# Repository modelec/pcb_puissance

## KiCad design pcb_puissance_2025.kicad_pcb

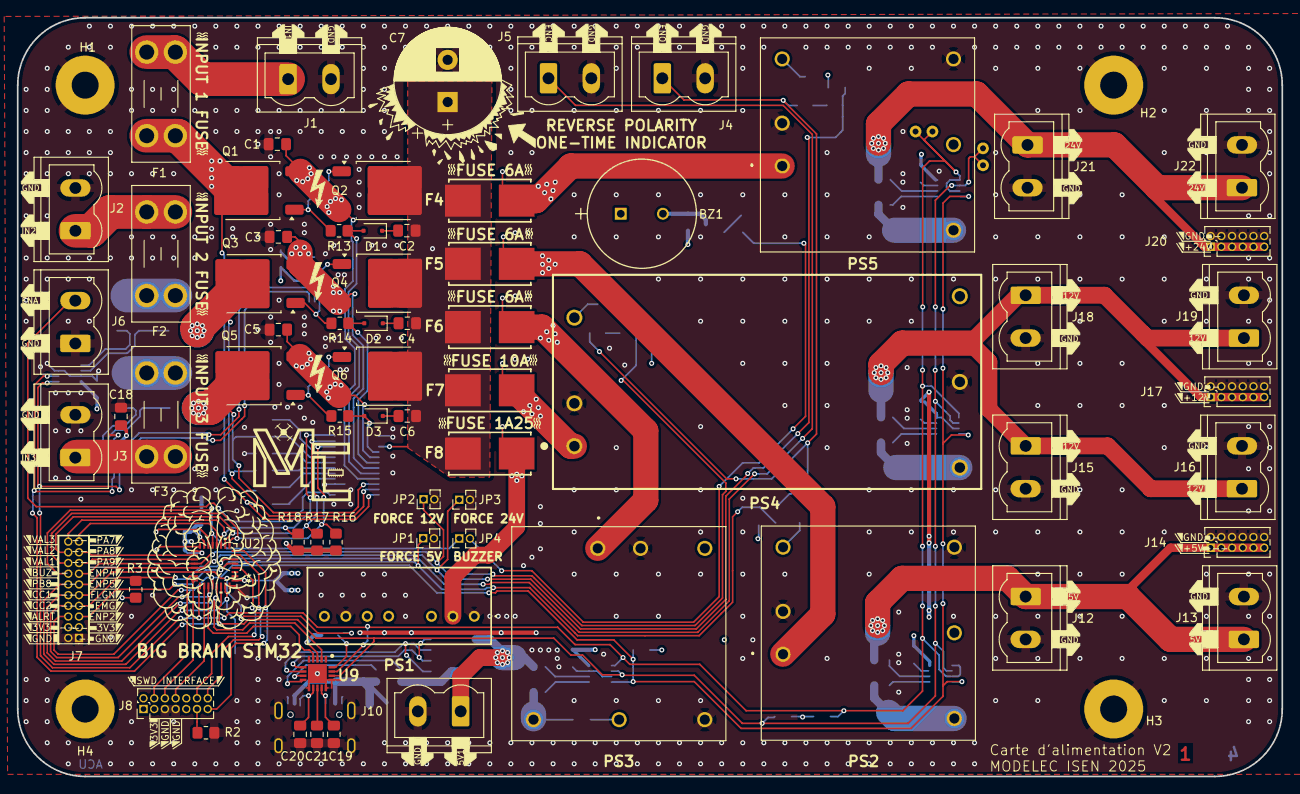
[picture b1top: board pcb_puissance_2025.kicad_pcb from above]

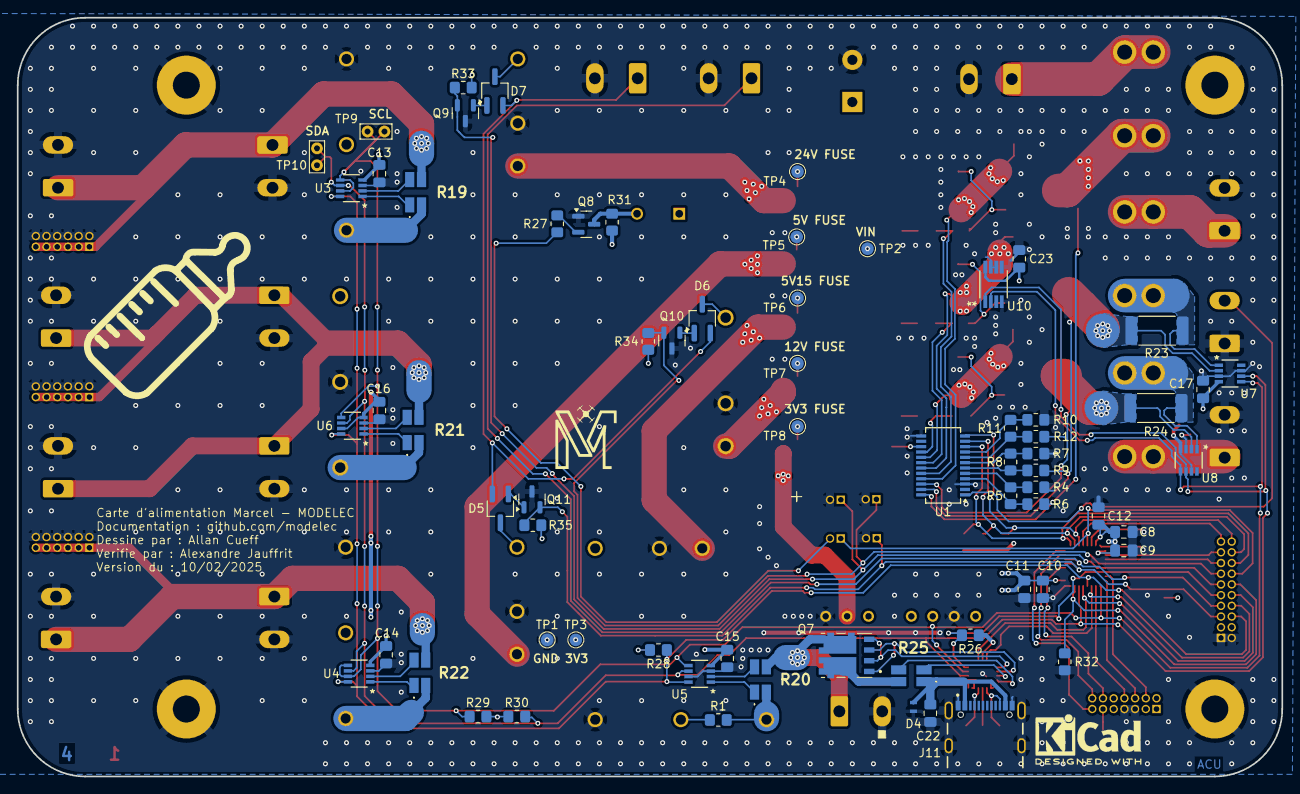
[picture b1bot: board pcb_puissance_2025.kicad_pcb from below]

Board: 4 copper layers, 150.0 x 90.0 mm, 139 parts (67 on the bottom side), 96 nets.

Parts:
BZ1: Buzzer; XTAL_PS1240P02BT_TDK
C1, C3, C5: 0u39; C_0805_2012Metric_Pad1.18x1.45mm_HandSolder
C2, C4, C6: 39n; C_0805_2012Metric_Pad1.18x1.45mm_HandSolder
C7: 1000u; CP_Radial_D12.5mm_P5.00mm
C8: 10n; C_0805_2012Metric_Pad1.18x1.45mm_HandSolder
C9, C10, C13, C14, C15, C16, C17, C18, C21, C23: 100n; C_0805_2012Metric_Pad1.18x1.45mm_HandSolder
C11: 4u7; C_0805_2012Metric_Pad1.18x1.45mm_HandSolder
C12: 1u; C_0805_2012Metric_Pad1.18x1.45mm_HandSolder
C19, C20: 330p; C_0805_2012Metric_Pad1.18x1.45mm_HandSolder
C22: 2u2; C_0805_2012Metric_Pad1.18x1.45mm_HandSolder
D1, D2, D3: BAT54J; D_SOD-323F
D4: ESDA25P35-1U1M; QFN1610_STM
D5, D6, D7: D_Dual_CommonAnode_AKK_Parallel; TSOT-23_HandSoldering
F1: 10A; Fuseholder_Blade_Mini_Keystone_3568
F2, F3: 20A; Fuseholder_Blade_Mini_Keystone_3568
F4, F5, F6: 6A; 01550900M
F7: 10A; 01550900M
F8: 1A25; 01550900M
H1, H2, H3, H4: MountingHole_Pad; MountingHole_3.2mm_M3_Pad
J1, J2, J3, J4, J5, J6, J10, J12, J13, J15, J16, J18, J19, J21, J22: 1755736; PhoenixContact_MSTBVA_2,5_2-G-5,08_1x02_P5.08mm_Vertical
J7: Conn_02x10_Odd_Even; PinHeader_2x10_P1.27mm_Vertical
J8: Conn_ST_STDC14; PinHeader_2x07_P1.27mm_Vertical
J11: USB_C_Receptacle_USB2.0_16P; GCT_USB4105-GF-A
J14, J17, J20: Conn_02x06_Odd_Even; PinHeader_2x06_P1.27mm_Vertical
JP1, JP2, JP3: Jumper_2_Open; PinHeader_1x02_P1.27mm_Vertical
JP4: Jumper_2_Bridged; PinHeader_1x02_P1.27mm_Vertical
PS1: TMR_6-2410WI; TMR60510
PS2, PS3: THN_30-2411WI; THN301211
PS4: TEN_50-2412WI; TEN_50-2411
PS5: THN_30-2415WI; THN301211
Q1, Q2, Q3, Q4, Q5, Q6: SUD50P06-15; TO-252-2
Q7: STL40DN3LLH5; TRANS_STL40DN3LLH5
Q8: NPN; SOT-23
Q9, Q10, Q11: NMOS; SOT-23
R1: 82k; R_0805_2012Metric_Pad1.20x1.40mm_HandSolder
R2: 100; R_0805_2012Metric_Pad1.20x1.40mm_HandSolder
R3, R16, R17, R18, R28, R32: 10k; R_0805_2012Metric_Pad1.20x1.40mm_HandSolder
R4: 63k4; R_0805_2012Metric_Pad1.20x1.40mm_HandSolder
R5: 158k; R_0805_2012Metric_Pad1.20x1.40mm_HandSolder
R6: 1960k; R_0805_2012Metric_Pad1.20x1.40mm_HandSolder
R7, R10: 37k4; R_0805_2012Metric_Pad1.20x1.40mm_HandSolder
R8, R11: 78k7; R_0805_2012Metric_Pad1.20x1.40mm_HandSolder
R9, R12: 1180k; R_0805_2012Metric_Pad1.20x1.40mm_HandSolder
R13, R14, R15: 11k5; R_0805_2012Metric_Pad1.20x1.40mm_HandSolder
R19: 62m 0.5%; L4CL1206LR013DNR
R20, R22: 13m 0.5%; L4CL1206LR013DNR
R21: 20m 0.5%; L4CL1206LR013DNR
R23, R24: 4m 0.5%; R_2512_6332Metric_Pad1.40x3.35mm_HandSolder
R25: 7m 1%; L4CL1206LR013DNR
R26: 47k; R_0805_2012Metric_Pad1.20x1.40mm_HandSolder
R27, R31, R33, R34, R35: 1k; R_0805_2012Metric_Pad1.20x1.40mm_HandSolder
R29, R30: 2k2; R_0805_2012Metric_Pad1.20x1.40mm_HandSolder
TP1, TP2, TP3, TP4, TP5, TP6, TP7, TP8: TestPoint; TestPoint_Pad_D1.5mm
TP9, TP10: TestPoint; TestPoint_Bridge_Pitch2.0mm_Drill0.7mm
U1: LTC4417IGN; SSOP-24_3.9x8.7mm_P0.635mm
U2: STM32G491KEU6
U3, U7, U8: INA236BIDDFR; SOT23-8_DDF_TEX
U4, U5, U6: INA236AIDDFR; SOT23-8_DDF_TEX
U9: TCPP02-M18; QFN50P350X350X60-19N-D
U10: MCP9808T-E/MS; MSOP8_MC_MCH

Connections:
/3V3: BZ1.1 (+), C8.1, C9.1, C10.1, C11.1, C12.1, C13.2, C14.2, C15.2, C16.2, C17.1, C18.1, C23.2, J7.3, J7.4, PS1.6 (+VOUT), R3.2, R16.1, R17.1, R18.1, R26.1, R28.2, R29.2, R30.1, R31.1, R33.2, R34.2, R35.2, TP3.1, U2.1 (VDD), U2.15 (VDDA), U2.17 (VDD), U3.4 (VS), U4.4 (VS), U5.4 (VS), U6.4 (VS), U6.7 (A0), U7.4 (VS), U8.4 (VS), U8.7 (A0), U9.3 (VCC_VCONN), U10.8 (VDD)
/Converters/5V: PS2.3 (+VOUT), R22.2
/Converters/5V15: PS3.3 (+VOUT), R1.2, R20.2
/Converters/5V_PILOT: J7.5, JP1.1 (A), Q11.2 (G), R35.1, U2.5 (PA0)
/Converters/12V: PS4.4 (+VOUT), R21.2
/Converters/12V_PILOT: J7.13, JP2.1 (A), Q10.2 (G), R34.1, U2.20 (PA10)
/Converters/24V: PS5.3 (+VOUT), R19.2
/Converters/24V_PILOT: J7.11, JP3.1 (A), Q9.2 (G), R33.1, U2.21 (PA11)
/Converters/EMERGENCY_STOP: D5.2 (K), D6.2 (K), D7.2 (K), J4.1
/Converters/VIN: C2.1, C4.1, C6.1, C7.1, F4.1, F5.1, F6.1, F7.1, F8.1, Q2.2 (D), Q4.2 (D), Q6.2 (D), TP2.1, U1.15 (VOUT)
/Microcontroller/24VALERT: J7.6, R28.1, U2.28 (PB5), U3.8 (ALERT), U4.8 (ALERT), U5.8 (ALERT), U6.8 (ALERT)
/Microcontroller/CC1: J7.10, U2.29 (PB6), U9.2 (CC1)
/Microcontroller/CC2: J7.8, U2.27 (PB4), U9.4 (CC2)
/Microcontroller/FLGN: J7.9, R26.2, U2.22 (PA12), U9.18 (FLGN)
/Microcontroller/PA1: J5.1, J7.7, R3.1, U2.6 (PA1)
/Microcontroller/PA7: J7.19, U2.12 (PA7)
/Microcontroller/PA8: J7.17, U2.18 (PA8)
/Microcontroller/PA9: J7.15, U2.19 (PA9)
/Microcontroller/PB0: J7.14, JP4.1 (A), U2.13 (PB0)
/Microcontroller/PB8: J7.12, R32.2, U2.31 (PB8-BOOT0)
/Microcontroller/SCL: R29.1, TP9.1, U2.25 (PA15), U3.5 (SCL), U3.7 (A0), U4.5 (SCL), U4.7 (A0), U5.5 (SCL), U6.5 (SCL), U7.5 (SCL), U8.5 (SCL), U9.17 (SCL), U10.2 (SCL)
/Microcontroller/SDA: R30.2, TP10.1, U2.30 (PB7), U3.6 (SDA), U4.6 (SDA), U5.6 (SDA), U6.6 (SDA), U7.6 (SDA), U8.6 (SDA), U9.16 (SDA), U10.1 (SDA)
/Microcontroller/VALID1: J7.16, R16.2, U1.10 (~VALID1), U2.9 (PA4)
/Microcontroller/VALID2: J7.18, R17.2, U1.11 (~VALID2), U2.10 (PA5)
/Microcontroller/VALID3: J7.20, R18.2, U1.12 (~VALID3), U2.11 (PA6)
/power_input_selector/EN: J6.2, U1.1 (EN)
/power_input_selector/VIN1: F1.2, Q1.2 (D), R6.1, U1.24 (V1)
/power_input_selector/VIN2: F2.2, R23.2, U7.1 (IN+)
/power_input_selector/VIN3: F3.1, R24.2, U8.1 (IN+)
GND: C1.2, C3.2, C5.2, C7.2, C8.2, C9.2, C10.2, C11.2, C12.2, C13.1, C14.1, C15.1, C16.1, C17.2, C18.2, C19.2, C20.1, C21.1, C22.2, C23.1, D4.2 (A), H1.1, H2.1, H3.1, H4.1, J1.2, J2.2, J3.2, J4.2, J5.2, J6.1, J7.1, J7.2, J8.5 (GND), J8.7 (GND), J10.2, J11.A1_B12 (GND), J11.B1_A12 (GND), J11.SH1 (SHIELD), J11.SH2, J11.SH3, J11.SH4, J12.2, J13.2, J14.2, J14.4, J14.6, J14.8, J14.10, J14.12, J15.2, J16.2, J17.2, J17.4, J17.6, J17.8, J17.10, J17.12, J18.2, J19.2, J20.2, J20.4, J20.6, J20.8, J20.10, J20.12, J21.2, J22.2, JP1.2 (B), JP2.2 (B), JP3.2 (B), PS1.1 (-VIN_(GND)), PS1.7 (-VOUT), PS2.2 (-VIN_(GND)), PS2.5 (-VOUT), PS3.2 (-VIN_(GND)), PS3.5 (-VOUT), PS4.2 (-VIN_(GND)), PS4.5 (-VOUT), PS5.2 (-VIN_(GND)), PS5.5 (-VOUT), Q8.1 (E), Q9.3 (D), Q10.3 (D), Q11.3 (D), R2.2, R4.2, R7.2, R10.2, R32.1, TP1.1, U1.3 (HYS), U1.13 (GND), U2.14 (VSSA), U2.16 (VSS), U2.32 (VSS), U3.3 (GND), U4.3 (GND), U5.3 (GND), U5.7 (A0), U6.3 (GND), U7.3 (GND), U7.7 (A0), U8.3 (GND), U9.10 (GND_1), U9.14 (GND_2), U9.15 (I2C_ADD), U9.19 (GND_3), U10.4 (GND), U10.5 (A2), U10.6 (A1), U10.7 (A0)
unnamed: BZ1.2 (-), Q8.3 (C), R31.2
unnamed: D1.2 (A), R13.2, U1.20 (G1)
unnamed: C2.2, D1.1 (K)
unnamed: D2.2 (A), R14.2, U1.18 (G2)
unnamed: C4.2, D2.1 (K)
unnamed: D3.2 (A), R15.2, U1.16 (G3)
unnamed: C6.2, D3.1 (K)
unnamed: C22.1, D4.1 (K), J11.A4_B9 (VBUS), J11.B4_A9 (VBUS), R25.1
unnamed: D5.3 (A), PS2.6 (REMOTE_ON/OFF)
unnamed: D6.3 (A), PS4.3 (REMOTE_ON/OFF)
unnamed: D7.3 (A), PS5.6 (REMOTE_ON/OFF)
unnamed: F1.1, J1.1
unnamed: F2.1, J2.1
unnamed: F3.2, J3.1
unnamed: J8.11 (GNDDetect), R2.1
unnamed: J8.6 (JCLK/SWCLK), U2.24 (PA14)
unnamed: J8.8 (JTDO/SWO), U2.26 (PB3)
unnamed: J8.4 (JTMS/SWDIO), U2.23 (PA13)
unnamed: J8.13 (VCP_RX), U2.8 (PA3)
unnamed: J8.14 (VCP_TX), U2.7 (PA2)
unnamed: J8.12 (~RST), U2.4 (PG10-NRST)
unnamed: J10.1, Q7.5-6, R20.3
unnamed: C19.1, J11.A5 (CC1), U9.13 (CC1C)
unnamed: C20.2, J11.B5 (CC2), U9.11 (CC2C)
unnamed: J12.1, J13.1, J14.1, J14.3, J14.5, J14.7, J14.9, J14.11, R22.3
unnamed: J15.1, J16.1, J17.1, J17.3, J17.5, J17.7, J17.9, J17.11, J18.1, J19.1, R21.3
unnamed: J20.1, J20.3, J20.5, J20.7, J20.9, J20.11, J21.1, J22.1, R19.3
unnamed: JP4.2 (B), R27.1
unnamed: F8.2, PS1.2 (+VIN_(VCC)), TP8.1
unnamed: F5.2, PS2.1 (+VIN_(VCC)), TP5.1
unnamed: F6.2, PS3.1 (+VIN_(VCC)), TP6.1
unnamed: PS3.4 (TRIM), R1.1
unnamed: F7.2, PS4.1 (+VIN_(VCC)), TP7.1
unnamed: F4.2, PS5.1 (+VIN_(VCC)), TP4.1
unnamed: Q1.1 (G), Q2.1 (G), R13.1
unnamed: C1.1, Q1.3 (S), Q2.3 (S), U1.21 (VS1)
unnamed: Q3.2 (D), R9.1, R23.1, U1.23 (V2), U7.2 (IN-)
unnamed: Q3.1 (G), Q4.1 (G), R14.1
unnamed: C3.1, Q3.3 (S), Q4.3 (S), U1.19 (VS2)
unnamed: Q5.2 (D), R12.1, R24.1, U1.22 (V3), U8.2 (IN-)
unnamed: Q5.1 (G), Q6.1 (G), R15.1
unnamed: C5.1, Q5.3 (S), Q6.3 (S), U1.17 (VS3)
unnamed: Q7.7-8, R25.4
unnamed: Q8.2 (B), R27.2
unnamed: D7.1 (K), Q9.1 (S)
unnamed: D6.1 (K), Q10.1 (S)
unnamed: D5.1 (K), Q11.1 (S)
unnamed: R4.1, R5.2, U1.5 (OV1)
unnamed: R7.1, R8.2, U1.7 (OV2)
unnamed: R10.1, R11.2, U1.9 (OV3)
unnamed: R5.1, R6.2, U1.4 (UV1)
unnamed: R8.1, R9.2, U1.6 (UV2)
unnamed: R11.1, R12.2, U1.8 (UV3)
unnamed: R19.1, U3.1 (IN+)
unnamed: R19.4, U3.2 (IN-)
unnamed: R22.1, U4.1 (IN+)
unnamed: R22.4, U4.2 (IN-)
unnamed: R20.1, U5.1 (IN+)
unnamed: R20.4, U5.2 (IN-)
unnamed: R21.1, U6.1 (IN+)
unnamed: R21.4, U6.2 (IN-)
unnamed: C21.2, U9.12 (CBIAS)
unnamed: Q7.2, Q7.4, U9.6 (GATE)
unnamed: R25.3, U9.9 (ISENSE)
unnamed: Q7.1, Q7.3, U9.7 (SRC)
unnamed: R25.2, U9.8 (VBUSC)

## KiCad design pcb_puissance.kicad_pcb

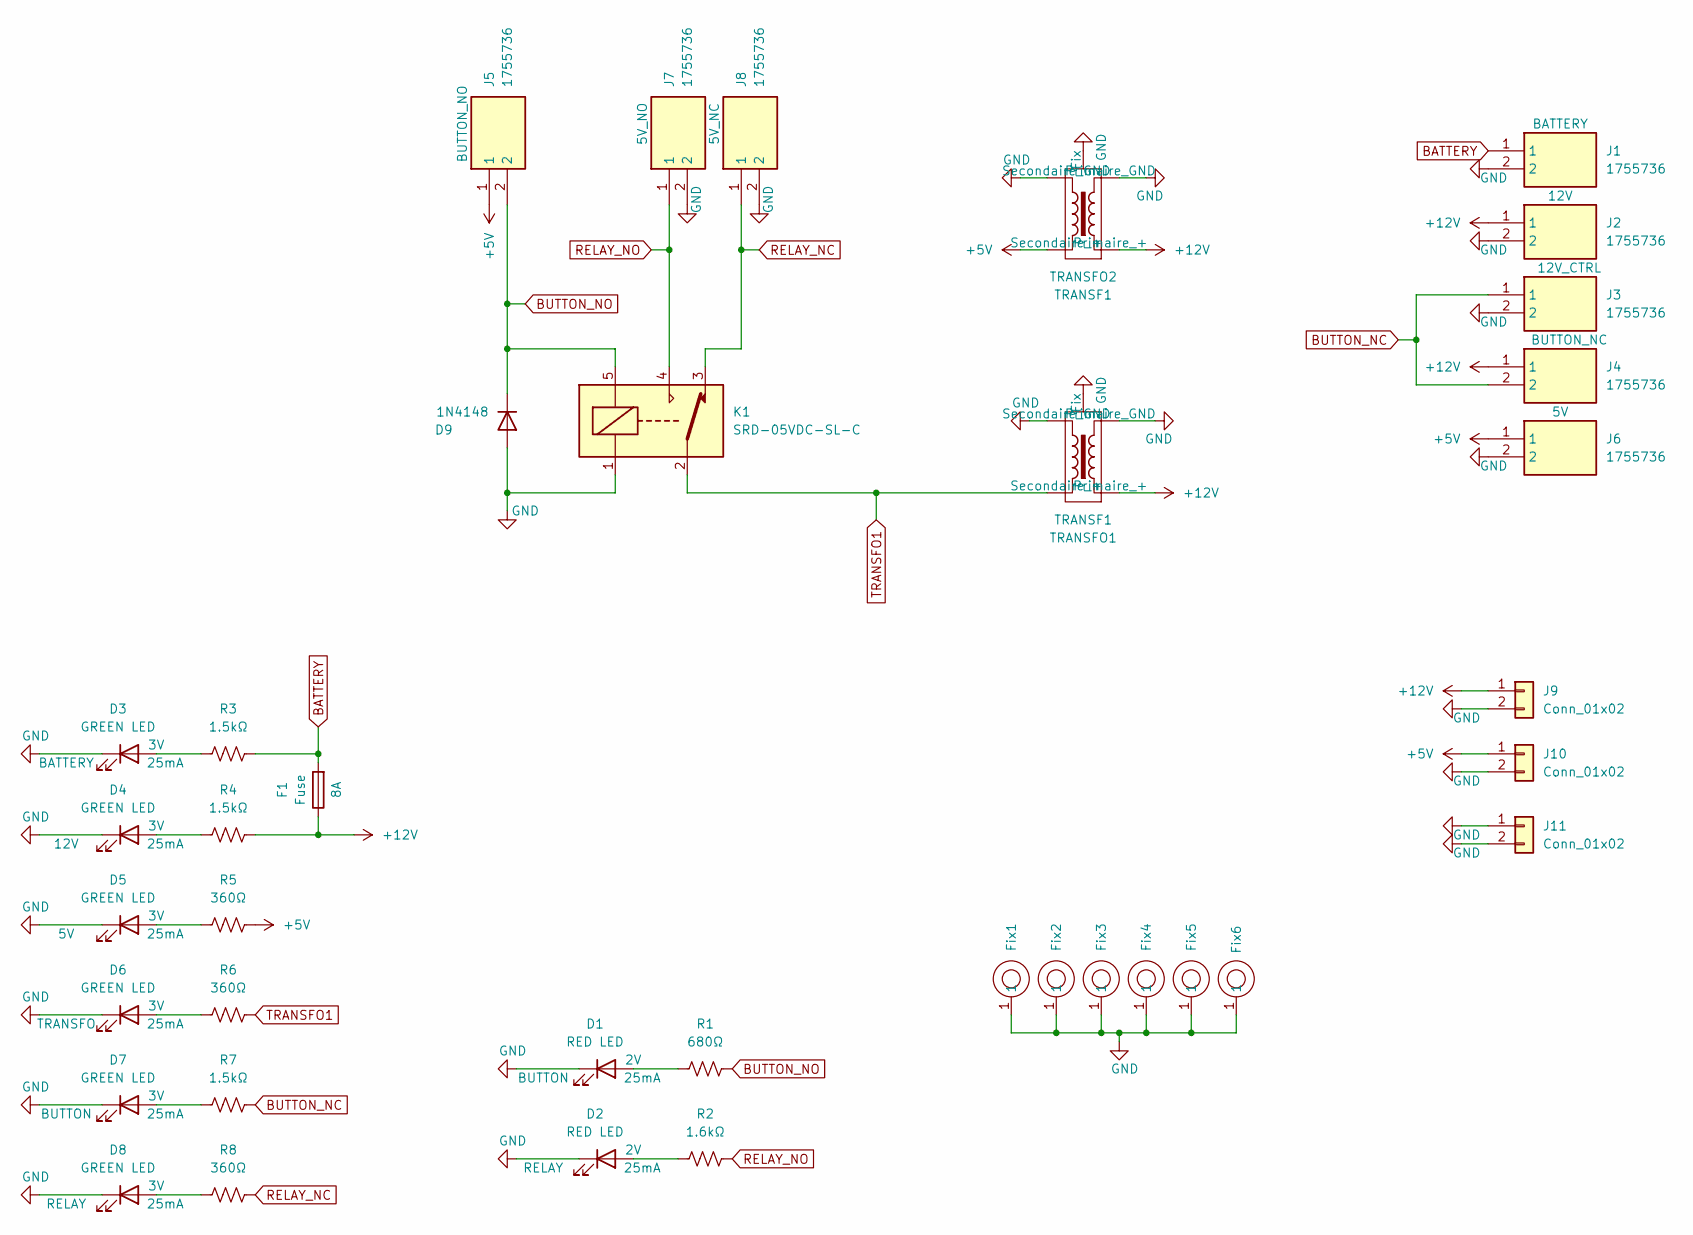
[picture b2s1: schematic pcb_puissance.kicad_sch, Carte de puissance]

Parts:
D1, D2: RED LED; LED_1206_3216Metric
D3, D4, D5, D6, D7, D8: GREEN LED; LED_1206_3216Metric
D9: 1N4148; D_DO-35_SOD27_P7.62mm_Horizontal
F1: Fuse; porte fusible E44
Fix1, Fix2, Fix3, Fix4, Fix5, Fix6: FIX3.2P7.5
J1, J2, J3, J4, J5, J6, J7, J8: 1755736; Manufacturer_Part_Number 1755736; Mouser Part Number 651-1755736
J9, J10, J11: Conn_01x02; PinHeader_1x02_P2.54mm_Vertical
K1: SRD-05VDC-SL-C
R1: 680Ω; R_0805_2012Metric
R2: 1.6kΩ; R_0805_2012Metric
R3, R4, R7: 1.5kΩ; R_0805_2012Metric
R5, R6, R8: 360Ω; R_0805_2012Metric
TRANSFO1, TRANSFO2: TRANSF1; transfo

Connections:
+5V: J5.1, J6.1, J10.1, R5.2, TRANSFO2.4 (Secondaire_+)
+12V: F1.1, J2.1, J4.1, J9.1, R4.2, TRANSFO1.1 (Primaire_+), TRANSFO2.1 (Primaire_+)
BATTERY: F1.2, J1.1, R3.2
BUTTON_NC: J3.1, J4.2, R7.2
BUTTON_NO: D9.1 (K), J5.2, K1.5, R1.2
GND: D1.1 (K), D2.1 (K), D3.1 (K), D4.1 (K), D5.1 (K), D6.1 (K), D7.1 (K), D8.1 (K), D9.2 (A), Fix1.1, Fix2.1, Fix3.1, Fix4.1, Fix5.1, Fix6.1, J1.2, J2.2, J3.2, J6.2, J7.2, J8.2, J9.2, J10.2, J11.1, J11.2, K1.1, TRANSFO1.2 (Primaire_GND), TRANSFO1.3 (Secondaire_GND), TRANSFO1.5 (Fix), TRANSFO2.2 (Primaire_GND), TRANSFO2.3 (Secondaire_GND), TRANSFO2.5 (Fix)
unnamed: D1.2 (A), R1.1
unnamed: D2.2 (A), R2.1
unnamed: D3.2 (A), R3.1
unnamed: D4.2 (A), R4.1
unnamed: D5.2 (A), R5.1
unnamed: D6.2 (A), R6.1
unnamed: D7.2 (A), R7.1
unnamed: D8.2 (A), R8.1
RELAY_NC: J8.1, K1.3, R8.2
RELAY_NO: J7.1, K1.4, R2.2
TRANSFO1: K1.2, R6.2, TRANSFO1.4 (Secondaire_+)

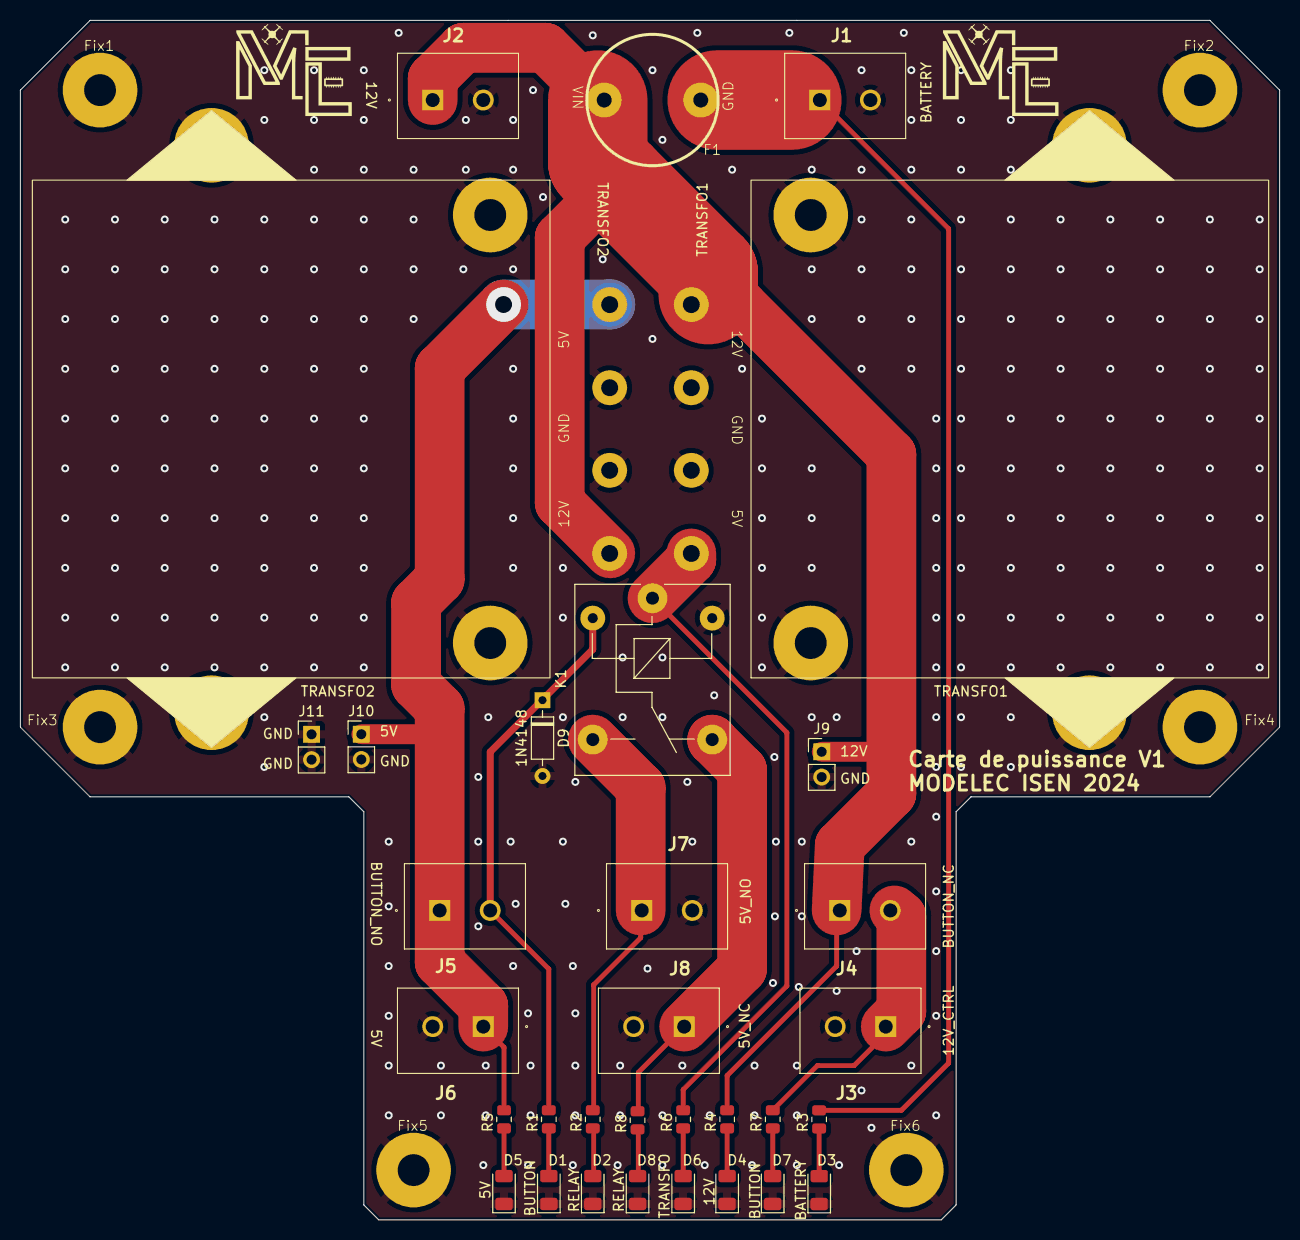
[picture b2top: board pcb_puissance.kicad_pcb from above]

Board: 2 copper layers, 126.5 x 120.5 mm, 38 parts (0 on the bottom side), 17 nets.

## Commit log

2023-12-20 Add KiCAD files
2023-12-20 changements connecteur CI + placement empreintes et routage PCB
2023-12-20 Fin routage + contour/plan de masse/entretoises propres.
2023-12-20 Agrandissement piste batterie -> 10mm
2023-12-21 Deplacement connecteurs, petites pistes 0.5mm, ajout connecteurs Dupond, plan de masse Front, pastilles pour les fixations
2023-12-22 Pastilles oubliées + ajout vias + plus d'espace pour les connecteurs
2023-12-22 Génération nouveaux fichiers fabrication
2023-12-22 Vias dans les pastilles + textes cachés par les connecteurs
2023-12-22 Fixations
2023-12-22 Remove #auto_saved_files#
2023-12-24 DRC, nettoyage pistes cachées, ajout logos
2023-12-24 Ajout noms transfos +visibles
2023-12-26 Rectification empreinte relai
2024-03-18 Correctifs version 1.2
2025-01-25 Nouveau PCB 2025
2025-01-29 PCB 2025 rev2
2025-02-10 nouvelle version : correction erreurs, ameliorations qualite, passage a 4 couches, ajout pilotage des traco depuis le stm32
2025-02-10 changements mineurs (BOM principalement)
2025-02-26 Correctifs et améliorations + passage à KiCad V9
